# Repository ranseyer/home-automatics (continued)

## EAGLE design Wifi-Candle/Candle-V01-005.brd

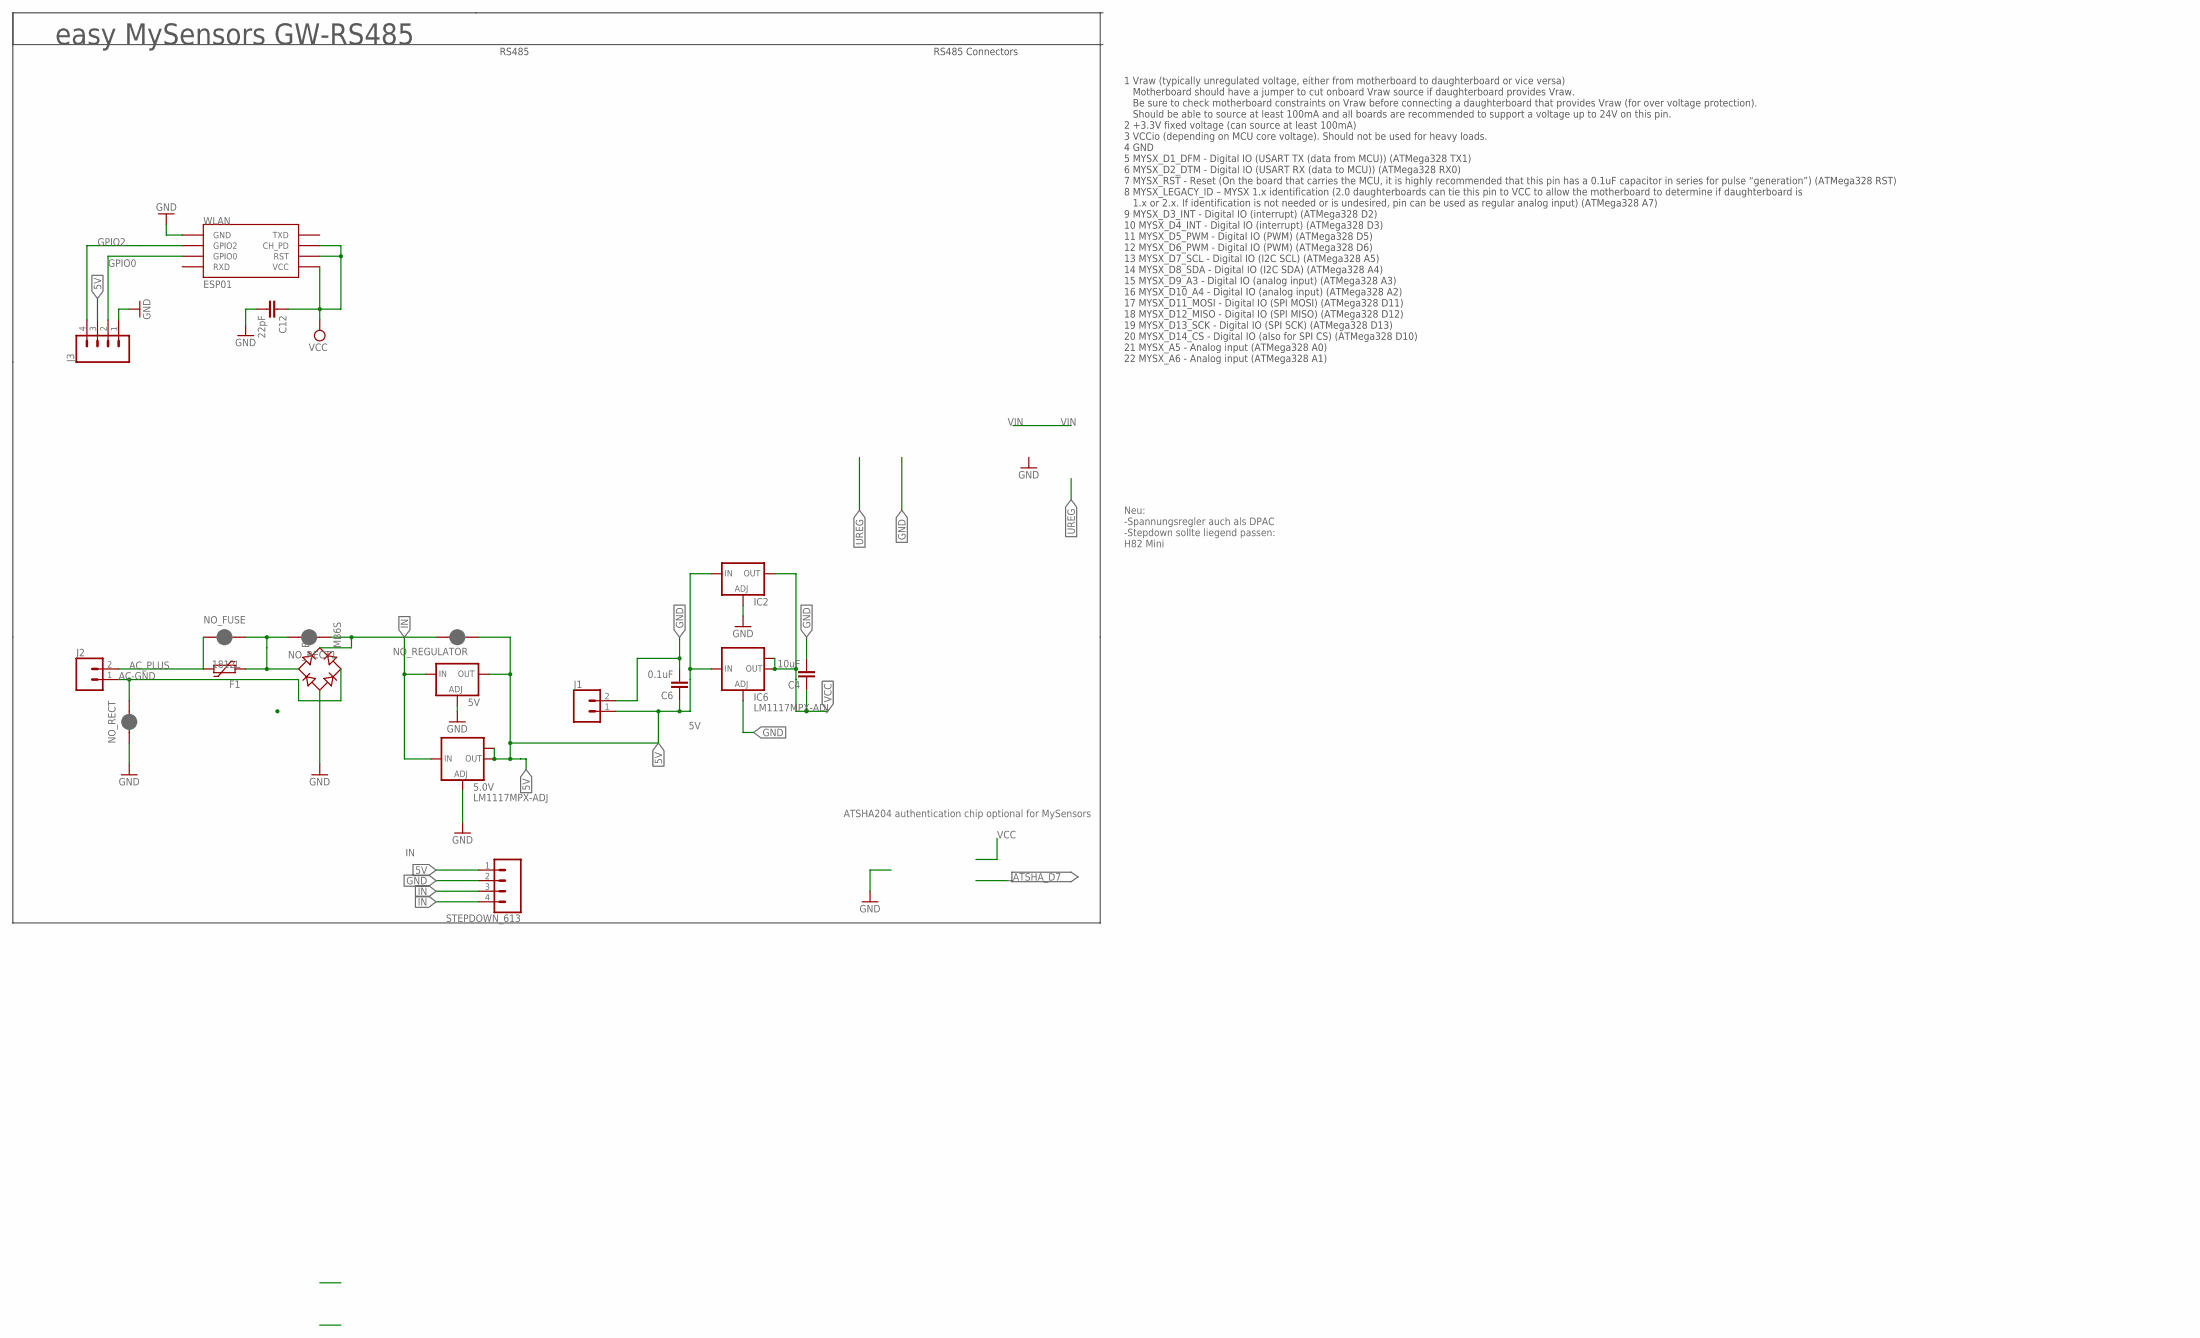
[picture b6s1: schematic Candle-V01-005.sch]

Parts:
5.0V: LM1117MPX-ADJ; SOT223
5V: LD117ADT50TR; DPACK
B1: MB6S; SOIC-4
C4: 10uF; C1210
C6: 0.1uF; C1206
C12: 22pF; C0805
F1: 1812L
IC2: LD117ADT50TR; DPACK
IC6: LM1117MPX-ADJ; SOT223
J1, J2: CONN_02PTH3; 1X02_LONGPADS
J3: CONN_04LONGPADS; 1X04_LONGPADS
NO_FUSE: JUMPER-SMT_2_NC_PASTE_NO-SILK; SMT-JUMPER_2_NC_PASTE_NO-SILK
NO_RECT, NO_RECT1: JUMPER-SMT_2_NC_PASTE_NO-SILK; SMT-JUMPER_2_NC_PASTE_NO-SILK
NO_REGULATOR: JUMPER-SMT_2_NC_PASTE_NO-SILK; SMT-JUMPER_2_NC_PASTE_NO-SILK
STEPDOWN_613: CONN_04; 1X04
WLAN: ESP01

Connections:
5V: 5.0V.2 (OUT), 5.0V.TAB (OUT1), 5V.4 (OUT), C6.1, IC2.3 (IN), IC6.3 (IN), J1.1, J3.3, NO_REGULATOR.1, STEPDOWN_613.1
AC-GND: B1.~2 (AC2), J2.1, NO_RECT.1
AC_PLUS: F1.P$2 (2), J2.2, NO_FUSE.2
GND: 5.0V.1 (ADJ), 5V.1 (ADJ), B1.-, C4.2, C6.2, C12.2, IC2.1 (ADJ), IC6.1 (ADJ), J1.2, J3.1, NO_RECT.2, STEPDOWN_613.2, WLAN.GND
GPIO0: J3.2, WLAN.GPIO0
GPIO2: J3.4, WLAN.GPIO2
IN: 5.0V.3 (IN), 5V.3 (IN), B1.+, NO_RECT1.2, NO_REGULATOR.2, STEPDOWN_613.3, STEPDOWN_613.4
unnamed: B1.~1 (AC1), F1.P$1 (1), NO_FUSE.1, NO_RECT1.1
VCC: C4.1, C12.1, IC2.4 (OUT), IC6.2 (OUT), IC6.TAB (OUT1), WLAN.CH_PD, WLAN.RST, WLAN.VCC

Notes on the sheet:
easy MySensors GW-RS485
ATSHA204 authentication chip optional for MySensors
Neu: -Spannungsregler auch als DPAC -Stepdown sollte liegend passen: H82 Mini
RS485
RS485 Connectors
1 Vraw (typically unregulated voltage, either from motherboard to daughterboard or vice versa) Motherboard should have a jumper to cut onboard Vraw source if daughterboard provides Vraw. Be sure to check motherboard constraints on Vraw before connecting a daughterboard that provides Vraw (for over 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

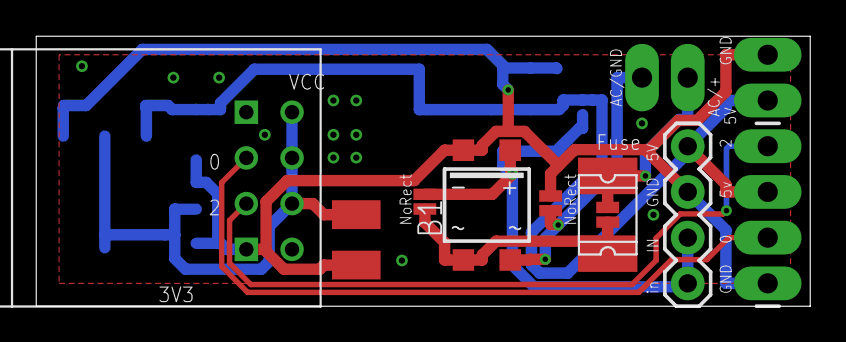
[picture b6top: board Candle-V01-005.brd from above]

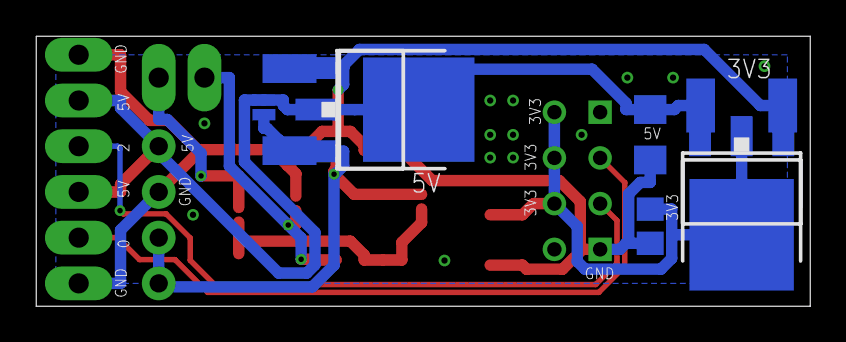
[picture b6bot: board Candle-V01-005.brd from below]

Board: 2 copper layers, 43.0 x 15.0 mm, 18 parts (7 on the bottom side), 9 nets.

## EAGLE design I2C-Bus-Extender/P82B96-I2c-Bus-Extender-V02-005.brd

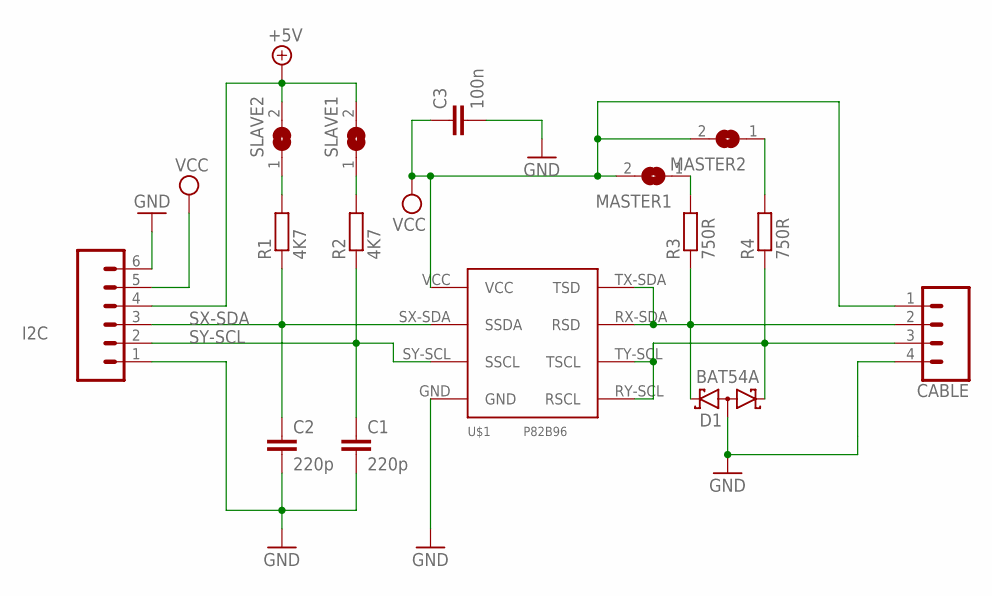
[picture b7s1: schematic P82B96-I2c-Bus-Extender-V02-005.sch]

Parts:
C1, C2: 220p; C0805K
C3: 100n; C0805K
CABLE: CONN_04LOCK_LONGPADS; 1X04_LOCK_LONGPADS
D1: BAT54A; SOT23
I2C: CONN_06LONGPADS; 1X06_LONGPADS
MASTER1, MASTER2: SJ
R1, R2: 4K7; R0805W
R3, R4: 750R; R0805W
SLAVE1, SLAVE2: SJ
U$1: P82B96-NEW; SOIC8

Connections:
+5V: I2C.4, SLAVE1.2, SLAVE2.2
GND: C1.2, C2.2, C3.2, CABLE.4, D1.3 (AA), I2C.1, I2C.6, U$1.GND
unnamed: R2.2, SLAVE1.1
unnamed: R1.2, SLAVE2.1
unnamed: MASTER2.1, R4.2
unnamed: MASTER1.1, R3.2
RX-SDA: CABLE.2, D1.2 (K2), R3.1, U$1.RX-SDA (RSD), U$1.TX-SDA (TSD)
SX-SDA: C2.1, I2C.3, R1.1, U$1.SX-SDA (SSDA)
SY-SCL: C1.1, I2C.2, R2.1, U$1.SY-SCL (SSCL)
TY-SCL: CABLE.3, D1.1 (K1), R4.1, U$1.RY-SCL (RSCL), U$1.TY-SCL (TSCL)
VCC: C3.1, CABLE.1, I2C.5, MASTER1.2, MASTER2.2, U$1.VCC

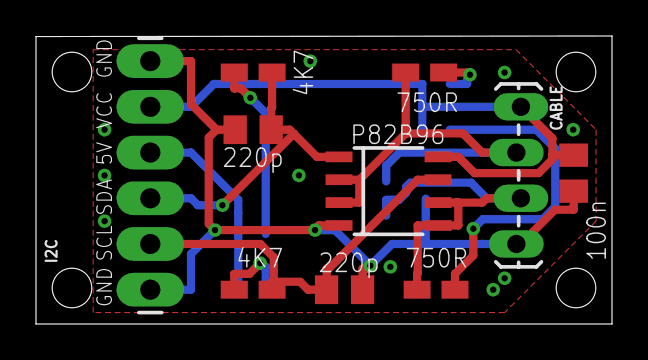
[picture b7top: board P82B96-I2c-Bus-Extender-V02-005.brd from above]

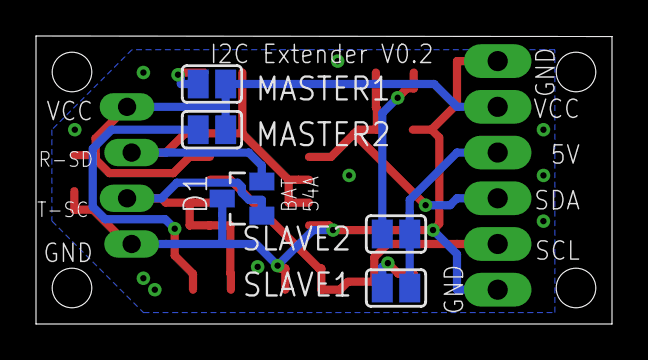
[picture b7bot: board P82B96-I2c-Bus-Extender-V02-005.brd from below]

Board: 2 copper layers, 32.0 x 16.0 mm, 15 parts (5 on the bottom side), 11 nets.

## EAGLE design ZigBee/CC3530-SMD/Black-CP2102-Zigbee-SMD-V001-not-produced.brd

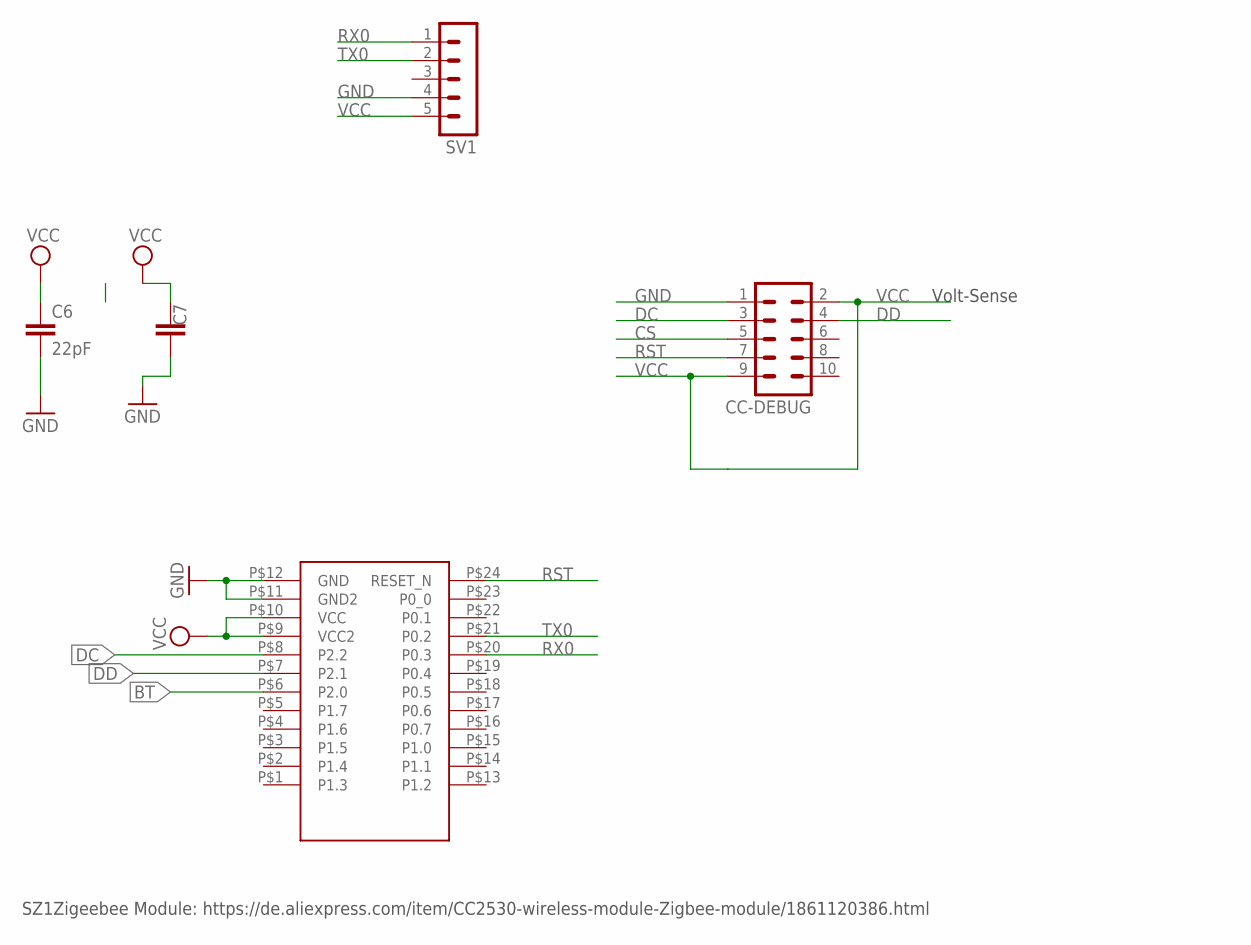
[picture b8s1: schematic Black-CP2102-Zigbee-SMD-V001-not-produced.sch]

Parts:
C6: 22pF; C0805
C7: C-EUC1812; C1812
CC-DEBUG: MA05-2
SV1: MA05-1
U$1: CC2530; SZ1ZIGBEE-SMD

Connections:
BT: U$1.P$6 (P2.0)
CS: CC-DEBUG.5
DC: CC-DEBUG.3, U$1.P$8 (P2.2)
DD: CC-DEBUG.4, U$1.P$7 (P2.1)
GND: C6.2, C7.1, CC-DEBUG.1, SV1.4, U$1.P$11 (GND2), U$1.P$12 (GND)
RST: CC-DEBUG.7, U$1.P$24 (RESET_N)
RX0: SV1.1, U$1.P$20 (P0.3)
TX0: SV1.2, U$1.P$21 (P0.2)
VCC: C6.1, C7.2, CC-DEBUG.2, CC-DEBUG.9, SV1.5, U$1.P$9 (VCC2), U$1.P$10 (VCC)

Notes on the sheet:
Volt-Sense
SZ1Zigeebee Module: https://de.aliexpress.com/item/CC2530-wireless-module-Zigbee-module/1861120386.html

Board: 2 copper layers, 5 parts (1 on the bottom side), 7 nets, no tracks yet.

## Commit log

2016-04-29 nanoCUL works
2016-04-29 Serial GW (mySensors)
2016-05-11 Wettersensor
2016-08-23 RGBWW
2016-09-18 H801 Sming-Test1
2016-09-18 H801 Readme
2016-10-15 Wintergarden-HW with own libs for levelshifter and 4xrelaisboard footprint
2016-10-26 MySenS GW2
2016-11-23 Nextion Display
2016-12-03 ESP-Link
2016-12-20 Doku
2017-01-04 H801 RGBWW Light
2017-02-15 Adapter Lvl Shifter
2017-02-15 Cleanup
2017-02-16 MySensors easyRS485
2017-02-24 MySensors easyRS485 Image-Exports
2017-03-05 MySensors easyRS485 V2
2017-04-14 Mains Voltage-Sensor
2017-05-12 MySens Gateways
2017-05-31 Rain-Sensors + some RS485 Boards
2017-06-17 Rain-Sensor: Calculation of the heating
2017-06-17 Rain-Sensor: Images
2017-06-29 Rain-Sensor: little fix
2017-07-08 Rain-Sensor: little fixes
2017-07-08 Rollershutter Test
2017-07-08 Rollershutter Test2
2017-07-28 MySysNanoGW-Node + Rain UweH
2017-08-22 MySens easy ProMini
2017-08-25 MySens easyProMini -Draft2
2017-08-29 MySens V01 (ordered)
2017-08-29 readme
2017-08-29 readme2
2017-08-29 More docu
2017-10-17 Some new easyBoards
2017-10-18 little fixes for new easyBoards
2017-10-31 MySensors moved to a new repo
2017-12-29 RS485 Termination
2017-12-29 Update RS485 Termin
2017-12-29 Rs485 Term
2017-12-29 rs485 Terminator update
2018-01-01 Rain Doku
2018-01-02 BOM Rainsensor
2018-01-28 Ambiligh-Levelshifter + LEDE Rectifier
2018-02-17 RFID Lock
    initial
2018-02-17 Lock
    Value in String
2018-02-17 Lock
    RS485
2018-02-17 Lock
    Presentation
2018-02-17 Lock
2018-02-28 test
2018-03-03 RFID Initial
2018-03-03 rfid
2018-03-03 rfid
    Found tag id: 0xF6,0xEA,0x25,0x3B,0x00,0x00,0x00
    Start
    0x246,0x234,0x37,0x59,0x00,0x00,0x00
    Ende
2018-03-04 rfid
    works but uggly
2018-03-04 rfid
    input von Betauser
2018-03-04 RFID OK without local Keys
2018-03-20 RFID-Lock works
2018-11-17 Zigbee Schematic Export
2018-11-17 Little fix
2018-12-05 Zigbee V02
2018-12-20 Deloghi Images
2018-12-27 url
    url
2019-04-29 Rain SW
2019-05-05 Water Sendsor
2019-05-06 Water-Sensor V01
2019-05-12 cc2530
2019-06-22 docu 1w water-sens
2019-11-08 Homematic-Wintergarten / WiFi Candle
2021-01-20 Power Supply + Cleanup
2021-01-29 WLED + HMModUART-CP2102
2021-02-15 pics
2021-04-12 Cleanup Homematic
